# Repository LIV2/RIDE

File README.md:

# 🏍 RIDE - A500+ Fast Ram + IDE
## IDE + 11.37 Megabyte Fast RAM for the A500/A1000/A2000/CDTV

## Features
- 11.37MB Fast RAM - 1.5MB $C0/Ranger + 8MB Fast + 1.87 Bonus ($A00000)
- Autoboot IDE, Kick 1.3 compatible Open Source driver [lide.device](https://github.com/LIV2/lide.device)
- [Supports up to 2TB drives](https://github.com/LIV2/lide.device/#large-drive-4gb-support)
- Supports ATAPI Devices (CD/DVD-ROM, Zip disk etc - no IDEFix needed)
- Boot from ZIP/LS-120 etc
- [Boot from CD-ROM*](https://github.com/LIV2/lide.device/#boot-from-cdrom)
- SCSI Direct, NSD, TD64 support

## Table of contents
1. [Compatibility](#compatibility)
2. [Jumper settings](#jumper-settings)
3. [Connections](#connections)
4. [Enabling A0 Bonus RAM](#enabling-a0-bonus-ram)
5. [Programming](#programming)
6. [Ordering PCBs](#ordering-pcbs)
    * [PCB Order details](#pcb-order-details)
    * [PCB Assembly](#pcb-assembly)
    * [Bill of Materials](#bill-of-materials)
7. [License](#license)

## Compatibility

Compatible with Kickstart 1.3 and up.

## Jumper settings

**IDE Off**: Close to disable IDE  
**RAM1/RAM2**: Autoconfig RAM configuration
|RAM1|RAM2|Size|
|-|-|----|
|Open|Open|**8 MB**|
|Closed|Open|**4 MB**|
|Open|Closed|**2 MB**|
|Closed|Closed|**Disable**|

## Connections
* **LED**: Activity LED  
* **OVR**: **(Optional)** if connected this will enable the Ranger ($C00000) and Bonus ($A00000) RAM regions.  
Connect OVR to Gary pin 29 or pin 17 of the side expansion port  
* **CFGIN/OUT**: These pins allow this device to co-exist with other Autoconfig devices.
If there are no other Autoconfig devices in your system you can just leave these unconnected.  
If there *are* other Autoconfig devices you will want to use one of these to add the device to the chain.<br /><br />
In the Amiga 2000 you can connect CFGIN to U606 Pin 8 which will add the device to the end of the chain but **NOTE: This takes up the config signal for the leftmost slot (CN601) so do NOT install a Zorro card there**

## Enabling A0 Bonus RAM
The A0 Bonus RAM is not automatically picked up by kickstart and needs to be added using one of the included utilities.  
Note that the `addmem` command from Aminet will **NOT** work - the memory is not enabled until a specific RIDE register is set to enable it

To add the A0 Bonus RAM to the system you will need to use the `addram` command included in the RIDE-Software adf/lha found under [Releases](https://github.com/LIV2/RIDE/releases/latest).

Alternatively you can add the `bootrom` module to a custom kickstart so that this is done automatically at every boot.

## Programming

Program the CPLD using the relevant .jed file below (Right-click, Save as)
|Model|File|
|-----|----|
|A500(+)<br />A1000<br />A2000|[RIDE.jed](https://github.com/LIV2/RIDE/raw/master/Binary/RIDE.jed)|
|CDTV|[RIDE-CDTV.jed](https://github.com/LIV2/RIDE/raw/master/Binary/RIDE-CDTV.jed)|

You can find instructions on how to do that [here](https://linuxjedi.co.uk/2020/12/01/programming-xilinx-jtag-from-a-raspberry-pi/)

The IDE ROM can be programmed by booting from the latest lide-update.adf [here](https://github.com/LIV2/LIDE.device/releases/latest).

## Ordering PCBs

Download the latest Gerbers.zip from the latest release listed on the right-hand side of this page.

Also included in the release are the placement and bom files needed for JLCPCB's assembly service

### PCB Order details
This PCB has been designed to JLCPCB's 4-layer capabilities so I recommend ordering from them

* Layers: 4
* Surface finish: ENIG
* Remove Order Number: Yes

### PCB Assembly
The release files include the relevant BOM and CPL files for JLCPCB's Assembly service  
You can use the following options:  
* PCBA Type: Economic
* Assembly side: Top side
* Confirm Parts Placement: Yes (I recommend checking that all ICs have pin 1 in the correct location etc)

### Bill of materials
**Note**:
* The BOM lists a Mill-Max part for the pin sockets, however you can substitute these for some 9.7mm pin sockets like [these](https://www.aliexpress.com/item/33019740866.html?spm=a2g0o.productlist.similar_items.43.4ce068b4xz903H&utparam-url=scene%3Aimage_search%7Cquery_from%3Adetail_bigimg&pdp_npi=4%40dis%21NZD%2116.79%217.71%21%21%219.24%214.24%21%402101c67a17357902339972308e0382%2167156399241%21sea%21NZ%210%21ABX)  
* The 39SF010 flash can be substituted with 39SF020 or 39SF040 in TSOP-32

[BOM](https://html-preview.github.io/?url=https://github.com/LIV2/RIDE/blob/master/Docs/RIDE_bom.html)  
[HTML Interactive BOM](https://html-preview.github.io/?url=https://github.com/LIV2/RIDE/blob/master/Docs/RIDE-ibom.html)

## Acknowledgements
Thanks to [SukkoPera](https://github.com/SukkoPera) for supporting my early IDE prototype.

## License

This project is licensed under the GPL-2.0 only license

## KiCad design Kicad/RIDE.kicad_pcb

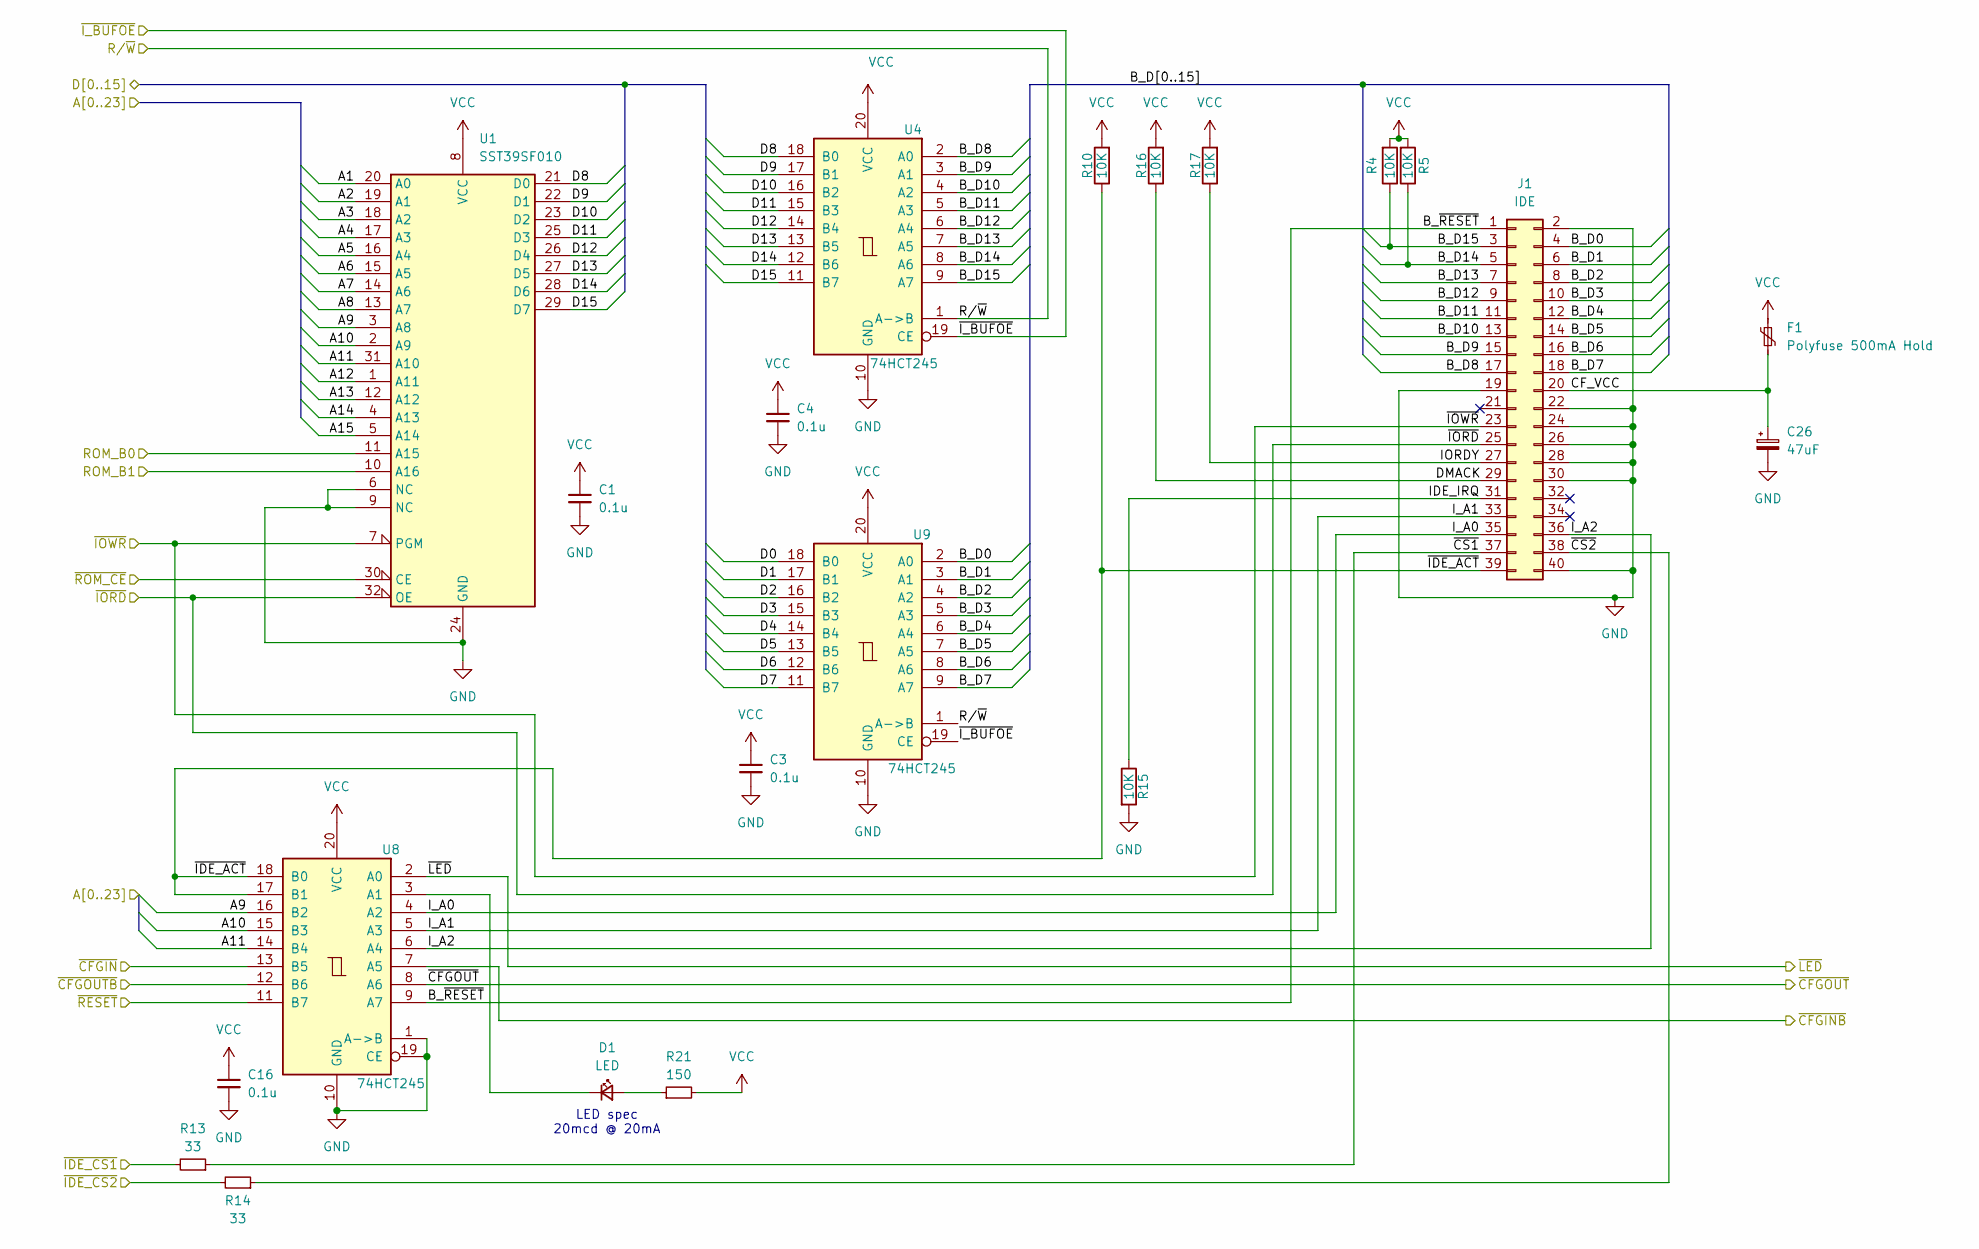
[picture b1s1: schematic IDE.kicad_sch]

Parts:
C1, C3, C4, C16: 0.1u; C_0603_1608Metric; Mouser # 80-C603C104K5RAC3121; LCSC # C14663
C26: 47uF; CP_EIA-3216-18_Kemet-A_Pad1.58x1.35mm_HandSolder; Mouser # 80-T490A476M10ATE1K; LCSC # C193224
D1: LED; LED_0603_1608Metric; Mouser # 696-SML-LX0603GW; LCSC # C136120
F1: Polyfuse 500mA Hold; Fuse_1206_3216Metric_Pad1.42x1.75mm_HandSolder; Mouser # 576-1206L110-16WR
J1: IDE; IDC-Header_2x20_P2.54mm_Vertical; Mouser # 737-BHR-40-VUA
R4, R5, R10, R15, R16, R17: 10K; R_0603_1608Metric; Mouser # 279-CRGH0603J10K; LCSC # C25804
R13, R14: 33; R_0603_1608Metric; Mouser # 279-CRG0603F33R; LCSC # C23140
R21: 150; R_0603_1608Metric; Mouser # 279-CRGP0603F150R; LCSC # C22808
U1: SST39SF010; TSOP-I-32_11.8x8mm_P0.5mm; Digikey # 150-SST39SF010A-70-4C-TU-ND
U4, U8, U9: 74HCT245; TSSOP-20_4.4x6.5mm_P0.65mm; Mouser # 595-SN74HCT245PWR; LCSC # C6779

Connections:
/CPLD/A1: U1.20 (A0); also elsewhere on the board
/CPLD/A2: U1.19 (A1); also elsewhere on the board
/CPLD/A3: U1.18 (A2); also elsewhere on the board
/CPLD/A4: U1.17 (A3); also elsewhere on the board
/CPLD/A5: U1.16 (A4); also elsewhere on the board
/CPLD/A6: U1.15 (A5); also elsewhere on the board
/CPLD/A7: U1.14 (A6); also elsewhere on the board
/CPLD/A8: U1.13 (A7); also elsewhere on the board
/CPLD/A9: U1.3 (A8), U8.16 (B2); also elsewhere on the board
/CPLD/A10: U1.2 (A9), U8.15 (B3); also elsewhere on the board
/CPLD/A11: U1.31 (A10), U8.14 (B4); also elsewhere on the board
/CPLD/A12: U1.1 (A11); also elsewhere on the board
/CPLD/A13: U1.12 (A12); also elsewhere on the board
/CPLD/A14: U1.4 (A13); also elsewhere on the board
/CPLD/A15: U1.5 (A14); also elsewhere on the board
/CPLD/D0: U9.18 (B0); also elsewhere on the board
/CPLD/D1: U9.17 (B1); also elsewhere on the board
/CPLD/D2: U9.16 (B2); also elsewhere on the board
/CPLD/D3: U9.15 (B3); also elsewhere on the board
/CPLD/D4: U9.14 (B4); also elsewhere on the board
/CPLD/D5: U9.13 (B5); also elsewhere on the board
/CPLD/D6: U9.12 (B6); also elsewhere on the board
/CPLD/D7: U9.11 (B7); also elsewhere on the board
/CPLD/D8: U1.21 (D0), U4.18 (B0); also elsewhere on the board
/CPLD/D9: U1.22 (D1), U4.17 (B1); also elsewhere on the board
/CPLD/D10: U1.23 (D2), U4.16 (B2); also elsewhere on the board
/CPLD/D11: U1.25 (D3), U4.15 (B3); also elsewhere on the board
/CPLD/D12: U1.26 (D4), U4.14 (B4); also elsewhere on the board
/CPLD/D13: U1.27 (D5), U4.13 (B5); also elsewhere on the board
/CPLD/D14: U1.28 (D6), U4.12 (B6); also elsewhere on the board
/CPLD/D15: U1.29 (D7), U4.11 (B7); also elsewhere on the board
/CPLD/ROM_B0: U1.11 (A15); also elsewhere on the board
/CPLD/ROM_B1: U1.10 (A16); also elsewhere on the board
/CPLD/R/~W: U4.1 (A->B), U9.1 (A->B); also elsewhere on the board
/CPLD/~CFGINB: U8.7 (A5); also elsewhere on the board
/CPLD/~CFGIN: U8.13 (B5); also elsewhere on the board
/CPLD/~CFGOUTB: U8.12 (B6); also elsewhere on the board
/CPLD/~IDE_CS1: R13.2; also elsewhere on the board
/CPLD/~IDE_CS2: R14.2; also elsewhere on the board
/CPLD/~I_BUFOE: U4.19 (CE), U9.19 (CE); also elsewhere on the board
/CPLD/~RESET: U8.11 (B7); also elsewhere on the board
/CPLD/~ROM_CE: U1.30 (CE); also elsewhere on the board
/IDE/B_D0: J1.4, U9.2 (A0)
/IDE/B_D1: J1.6, U9.3 (A1)
/IDE/B_D2: J1.8, U9.4 (A2)
/IDE/B_D3: J1.10, U9.5 (A3)
/IDE/B_D4: J1.12, U9.6 (A4)
/IDE/B_D5: J1.14, U9.7 (A5)
/IDE/B_D6: J1.16, U9.8 (A6)
/IDE/B_D7: J1.18, U9.9 (A7)
/IDE/B_D8: J1.17, U4.2 (A0)
/IDE/B_D9: J1.15, U4.3 (A1)
/IDE/B_D10: J1.13, U4.4 (A2)
/IDE/B_D11: J1.11, U4.5 (A3)
/IDE/B_D12: J1.9, U4.6 (A4)
/IDE/B_D13: J1.7, U4.7 (A5)
/IDE/B_D14: J1.5, R5.1, U4.8 (A6)
/IDE/B_D15: J1.3, R4.1, U4.9 (A7)
/IDE/B_~RESET: J1.1, U8.9 (A7)
/IDE/CF_VCC: C26.1, F1.2, J1.20
/IDE/DMACK: J1.29, R16.1
/IDE/IDE_IRQ: J1.31, R15.1
/IDE/IORDY: J1.27, R17.1
/IDE/I_A0: J1.35, U8.4 (A2)
/IDE/I_A1: J1.33, U8.5 (A3)
/IDE/I_A2: J1.36, U8.6 (A4)
/IDE/~CFGOUT: U8.8 (A6); also elsewhere on the board
/IDE/~CS1: J1.37, R13.1
/IDE/~CS2: J1.38, R14.1
/IDE/~IDE_ACT: J1.39, R10.1, U8.17 (B1), U8.18 (B0)
/IDE/~IORD: J1.25, U1.32 (OE); also elsewhere on the board
/IDE/~IOWR: J1.23, U1.7 (PGM); also elsewhere on the board
/IDE/~LED: U8.2 (A0); also elsewhere on the board
GND: C1.2, C3.2, C4.2, C16.2, C26.2, J1.2, J1.19, J1.22, J1.24, J1.26, J1.28, J1.30, J1.40, R15.2, U1.6 (NC), U1.9 (NC), U1.24 (GND), U4.10 (GND), U8.1 (A->B), U8.10 (GND), U8.19 (CE), U9.10 (GND); also elsewhere on the board
unnamed: D1.2 (A), R21.1
unnamed: D1.1 (K), U8.3 (A1)
VCC: C1.1, C3.1, C4.1, C16.1, F1.1, R4.2, R5.2, R10.2, R16.2, R17.2, R21.2, U1.8 (VCC), U4.20 (VCC), U8.20 (VCC), U9.20 (VCC); also elsewhere on the board

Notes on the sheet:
LED spec 20mcd @ 20mA

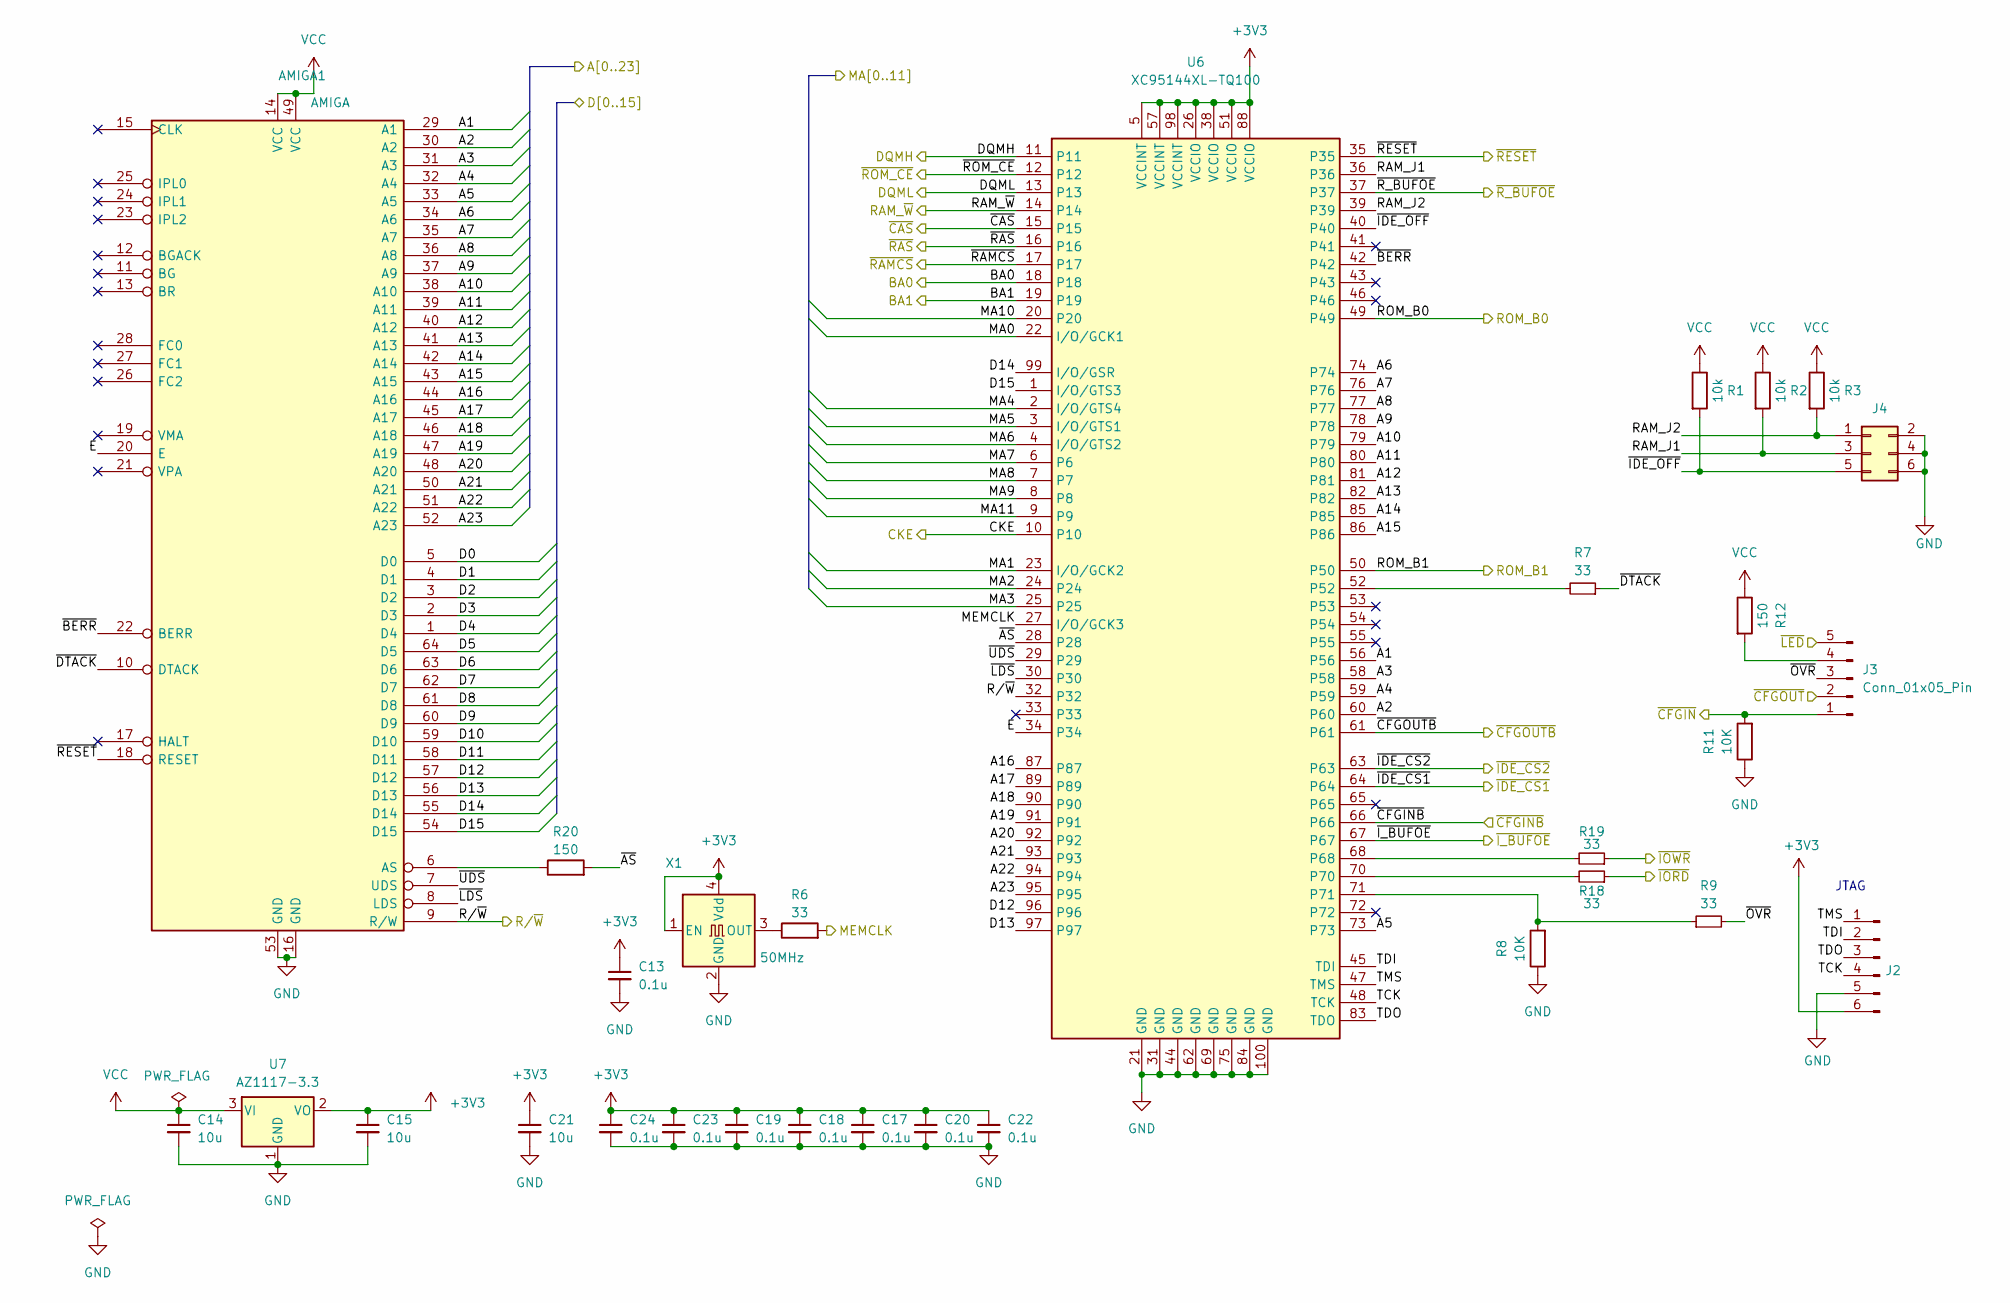
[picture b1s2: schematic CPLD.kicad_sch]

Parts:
AMIGA1: AMIGA; DIP-64_W22.86mm; Mouser # 575-643166
C13, C17, C18, C19, C20, C22, C23, C24: 0.1u; C_0603_1608Metric; Mouser # 80-C603C104K5RAC3121; LCSC # C14663
C14, C15: 10u; CP_EIA-3216-18_Kemet-A; Mouser # 80-T491A106M020; LCSC # C117023
C21: 10u; C_0805_2012Metric_Pad1.18x1.45mm_HandSolder; Mouser # 187-CL21A106KQFNNWE; LCSC # C15850
J2: Conn_01x06_Male; PinHeader_1x06_P2.54mm_Vertical
J3: Conn_01x05_Pin; PinHeader_1x05_P2.54mm_Vertical
J4: Conn_02x03_Odd_Even; PinHeader_2x03_P2.54mm_Vertical; Mouser # 571-4-146262-1
R1, R2, R3: 10k; R_0603_1608Metric; Mouser # 279-CRGH0603J10K; LCSC # C25804
R6, R7, R9, R18, R19: 33; R_0603_1608Metric; Mouser # 279-CRG0603F33R; LCSC # C23140
R8, R11: 10K; R_0603_1608Metric; Mouser # 279-CRGH0603J10K; LCSC # C25804
R12, R20: 150; R_0603_1608Metric; Mouser # 279-CRGP0603F150R; LCSC # C22808
U6: XC95144XL-TQ100; TQFP-100_14x14mm_P0.5mm; Mouser # 217-5144XL-10TQG100I; LCSC # C45126
U7: AZ1117-3.3; SOT-89-3; Mouser # 621-AZ1117CR-3.3TRG1; LCSC # C460428
X1: 50MHz; Oscillator_SMD_Abracon_ASE-4Pin_3.2x2.5mm; Mouser # 520-ECS-2333-500-BNT; LCSC # C5203552

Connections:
+3V3: C13.1, C15.1, C17.1, C18.1, C19.1, C20.1, C21.1, C22.1, C23.1, C24.1, J2.6, U6.5 (VCCINT), U6.26 (VCCIO), U6.38 (VCCIO), U6.51 (VCCIO), U6.57 (VCCINT), U6.88 (VCCIO), U6.98 (VCCINT), U7.2 (VO), X1.1 (EN), X1.4 (Vdd); also elsewhere on the board
/CPLD/A1: AMIGA1.29 (A1), U6.56; also elsewhere on the board
/CPLD/A2: AMIGA1.30 (A2), U6.60; also elsewhere on the board
/CPLD/A3: AMIGA1.31 (A3), U6.58; also elsewhere on the board
/CPLD/A4: AMIGA1.32 (A4), U6.59; also elsewhere on the board
/CPLD/A5: AMIGA1.33 (A5), U6.73; also elsewhere on the board
/CPLD/A6: AMIGA1.34 (A6), U6.74; also elsewhere on the board
/CPLD/A7: AMIGA1.35 (A7), U6.76; also elsewhere on the board
/CPLD/A8: AMIGA1.36 (A8), U6.77; also elsewhere on the board
/CPLD/A9: AMIGA1.37 (A9), U6.78; also elsewhere on the board
/CPLD/A10: AMIGA1.38 (A10), U6.79; also elsewhere on the board
/CPLD/A11: AMIGA1.39 (A11), U6.80; also elsewhere on the board
/CPLD/A12: AMIGA1.40 (A12), U6.81; also elsewhere on the board
/CPLD/A13: AMIGA1.41 (A13), U6.82; also elsewhere on the board
/CPLD/A14: AMIGA1.42 (A14), U6.85; also elsewhere on the board
/CPLD/A15: AMIGA1.43 (A15), U6.86; also elsewhere on the board
/CPLD/A16: AMIGA1.44 (A16), U6.87
/CPLD/A17: AMIGA1.45 (A17), U6.89
/CPLD/A18: AMIGA1.46 (A18), U6.90
/CPLD/A19: AMIGA1.47 (A19), U6.91
/CPLD/A20: AMIGA1.48 (A20), U6.92
/CPLD/A21: AMIGA1.50 (A21), U6.93
/CPLD/A22: AMIGA1.51 (A22), U6.94
/CPLD/A23: AMIGA1.52 (A23), U6.95
/CPLD/BA0: U6.18; also elsewhere on the board
/CPLD/BA1: U6.19; also elsewhere on the board
/CPLD/CKE: U6.10; also elsewhere on the board
/CPLD/D0: AMIGA1.5 (D0); also elsewhere on the board
/CPLD/D1: AMIGA1.4 (D1); also elsewhere on the board
/CPLD/D2: AMIGA1.3 (D2); also elsewhere on the board
/CPLD/D3: AMIGA1.2 (D3); also elsewhere on the board
/CPLD/D4: AMIGA1.1 (D4); also elsewhere on the board
/CPLD/D5: AMIGA1.64 (D5); also elsewhere on the board
/CPLD/D6: AMIGA1.63 (D6); also elsewhere on the board
/CPLD/D7: AMIGA1.62 (D7); also elsewhere on the board
/CPLD/D8: AMIGA1.61 (D8); also elsewhere on the board
/CPLD/D9: AMIGA1.60 (D9); also elsewhere on the board
/CPLD/D10: AMIGA1.59 (D10); also elsewhere on the board
/CPLD/D11: AMIGA1.58 (D11); also elsewhere on the board
/CPLD/D12: AMIGA1.57 (D12), U6.96; also elsewhere on the board
/CPLD/D13: AMIGA1.56 (D13), U6.97; also elsewhere on the board
/CPLD/D14: AMIGA1.55 (D14), U6.99 (I/O/GSR); also elsewhere on the board
/CPLD/D15: AMIGA1.54 (D15), U6.1 (I/O/GTS3); also elsewhere on the board
/CPLD/DQMH: U6.11; also elsewhere on the board
/CPLD/DQML: U6.13; also elsewhere on the board
/CPLD/E: AMIGA1.20 (E), U6.34
/CPLD/MA0: U6.22 (I/O/GCK1); also elsewhere on the board
/CPLD/MA1: U6.23 (I/O/GCK2); also elsewhere on the board
/CPLD/MA2: U6.24; also elsewhere on the board
/CPLD/MA3: U6.25; also elsewhere on the board
/CPLD/MA4: U6.2 (I/O/GTS4); also elsewhere on the board
/CPLD/MA5: U6.3 (I/O/GTS1); also elsewhere on the board
/CPLD/MA6: U6.4 (I/O/GTS2); also elsewhere on the board
/CPLD/MA7: U6.6; also elsewhere on the board
/CPLD/MA8: U6.7; also elsewhere on the board
/CPLD/MA9: U6.8; also elsewhere on the board
/CPLD/MA10: U6.20; also elsewhere on the board
/CPLD/MA11: U6.9; also elsewhere on the board
/CPLD/MEMCLK: R6.2, U6.27 (I/O/GCK3); also elsewhere on the board
/CPLD/RAM_J1: J4.3, R2.2, U6.36
/CPLD/RAM_J2: J4.1, R3.2, U6.39
/CPLD/RAM_~W: U6.14; also elsewhere on the board
/CPLD/ROM_B0: U6.49; also elsewhere on the board
/CPLD/ROM_B1: U6.50; also elsewhere on the board
/CPLD/R/~W: AMIGA1.9 (R/W), U6.32; also elsewhere on the board
/CPLD/TCK: J2.4, U6.48 (TCK)
/CPLD/TDI: J2.2, U6.45 (TDI)
/CPLD/TDO: J2.3, U6.83 (TDO)
/CPLD/TMS: J2.1, U6.47 (TMS)
/CPLD/~AS: R20.2, U6.28
/CPLD/~BERR: AMIGA1.22 (BERR), U6.42
/CPLD/~CAS: U6.15; also elsewhere on the board
/CPLD/~CFGINB: U6.66; also elsewhere on the board
/CPLD/~CFGIN: J3.1, R11.2; also elsewhere on the board
/CPLD/~CFGOUTB: U6.61; also elsewhere on the board
/CPLD/~DTACK: AMIGA1.10 (DTACK), R7.1
/CPLD/~IDE_CS1: U6.64; also elsewhere on the board
/CPLD/~IDE_CS2: U6.63; also elsewhere on the board
/CPLD/~IDE_OFF: J4.5, R1.2, U6.40
/CPLD/~I_BUFOE: U6.67; also elsewhere on the board
/CPLD/~LDS: AMIGA1.8 (LDS), U6.30
/CPLD/~OVR: J3.3, R9.2
/CPLD/~RAMCS: U6.17; also elsewhere on the board
/CPLD/~RAS: U6.16; also elsewhere on the board
/CPLD/~RESET: AMIGA1.18 (RESET), U6.35; also elsewhere on the board
/CPLD/~ROM_CE: U6.12; also elsewhere on the board
/CPLD/~R_BUFOE: U6.37; also elsewhere on the board
/CPLD/~UDS: AMIGA1.7 (UDS), U6.29
/IDE/~CFGOUT: J3.2; also elsewhere on the board
/IDE/~IORD: R18.1; also elsewhere on the board
/IDE/~IOWR: R19.1; also elsewhere on the board
/IDE/~LED: J3.5; also elsewhere on the board
GND: AMIGA1.16 (GND), AMIGA1.53 (GND), C13.2, C14.2, C15.2, C17.2, C18.2, C19.2, C20.2, C21.2, C22.2, C23.2, C24.2, J2.5, J4.2, J4.4, J4.6, R8.1, R11.1, U6.21 (GND), U6.31 (GND), U6.44 (GND), U6.62 (GND), U6.69 (GND), U6.75 (GND), U6.84 (GND), U6.100 (GND), U7.1 (GND), X1.2 (GND); also elsewhere on the board
unnamed: AMIGA1.6 (AS), R20.1
unnamed: J3.4, R12.2
unnamed: R7.2, U6.52
unnamed: R19.2, U6.68
unnamed: R18.2, U6.70
unnamed: R8.2, R9.1, U6.71
unnamed: R6.1, X1.3 (OUT)
VCC: AMIGA1.14 (VCC), AMIGA1.49 (VCC), C14.1, R1.1, R2.1, R3.1, R12.1, U7.3 (VI); also elsewhere on the board

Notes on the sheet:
JTAG

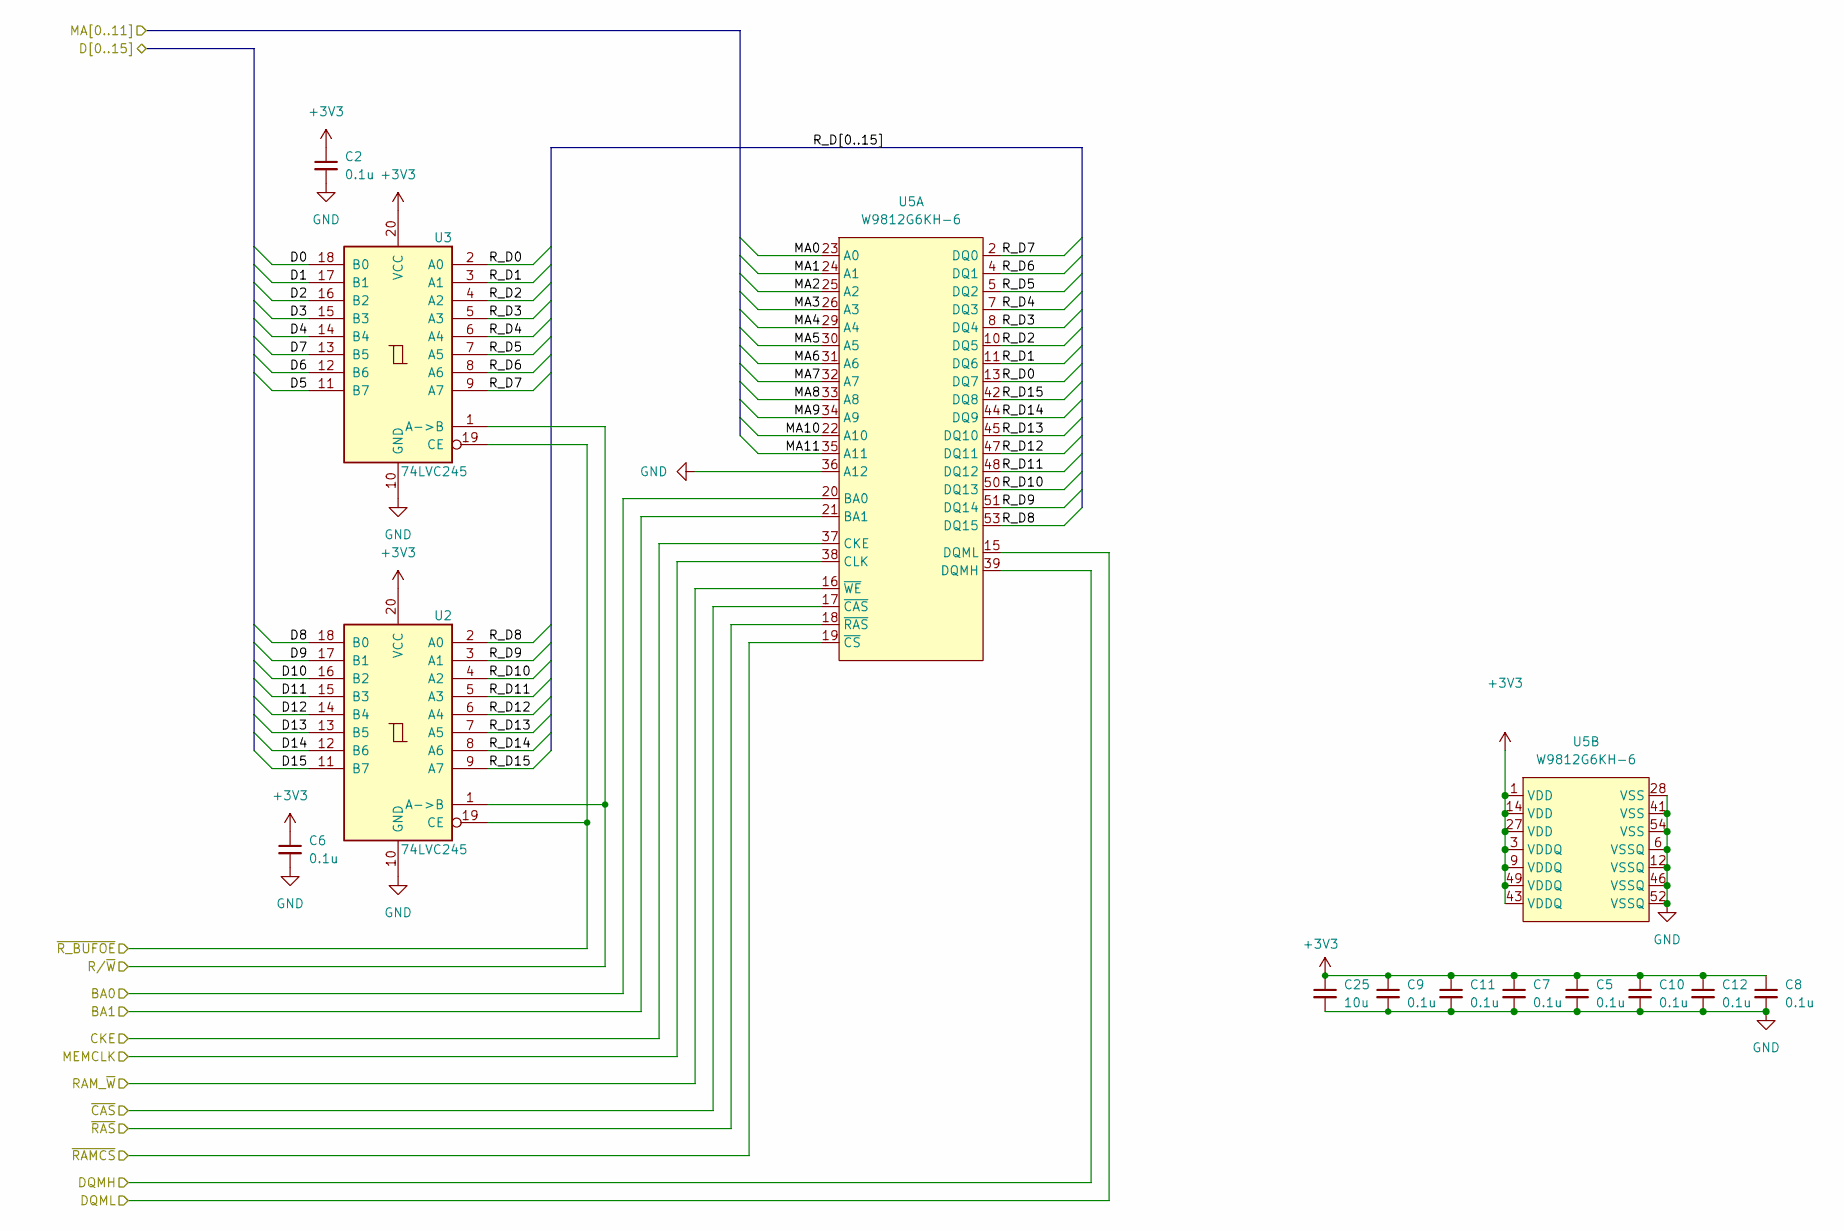
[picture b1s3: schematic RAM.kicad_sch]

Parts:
C2, C5, C6, C7, C8, C9, C10, C11, C12: 0.1u; C_0603_1608Metric; Mouser # 80-C603C104K5RAC3121; LCSC # C14663
C25: 10u; C_0805_2012Metric_Pad1.18x1.45mm_HandSolder; Mouser # 187-CL21A106KQFNNWE; LCSC # C15850
U2, U3: 74LVC245; TSSOP-20_4.4x6.5mm_P0.65mm; Mouser # 595-SN74LVC245APWR; LCSC # C7848
U5: W9812G6KH-6; TSOP-II-54_22.2x10.16mm_P0.8mm; Mouser # 454-W9812G6KH-6; LCSC # C62379

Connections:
+3V3: C2.1, C5.1, C6.1, C7.1, C8.1, C9.1, C10.1, C11.1, C12.1, C25.1, U2.20 (VCC), U3.20 (VCC), U5.1 (VDD), U5.3 (VDDQ), U5.9 (VDDQ), U5.14 (VDD), U5.27 (VDD), U5.43 (VDDQ), U5.49 (VDDQ); also elsewhere on the board
/CPLD/BA0: U5.20 (BA0); also elsewhere on the board
/CPLD/BA1: U5.21 (BA1); also elsewhere on the board
/CPLD/CKE: U5.37 (CKE); also elsewhere on the board
/CPLD/D0: U3.18 (B0); also elsewhere on the board
/CPLD/D1: U3.17 (B1); also elsewhere on the board
/CPLD/D2: U3.16 (B2); also elsewhere on the board
/CPLD/D3: U3.15 (B3); also elsewhere on the board
/CPLD/D4: U3.14 (B4); also elsewhere on the board
/CPLD/D5: U3.11 (B7); also elsewhere on the board
/CPLD/D6: U3.12 (B6); also elsewhere on the board
/CPLD/D7: U3.13 (B5); also elsewhere on the board
/CPLD/D8: U2.18 (B0); also elsewhere on the board
/CPLD/D9: U2.17 (B1); also elsewhere on the board
/CPLD/D10: U2.16 (B2); also elsewhere on the board
/CPLD/D11: U2.15 (B3); also elsewhere on the board
/CPLD/D12: U2.14 (B4); also elsewhere on the board
/CPLD/D13: U2.13 (B5); also elsewhere on the board
/CPLD/D14: U2.12 (B6); also elsewhere on the board
/CPLD/D15: U2.11 (B7); also elsewhere on the board
/CPLD/DQMH: U5.39 (DQMH); also elsewhere on the board
/CPLD/DQML: U5.15 (DQML); also elsewhere on the board
/CPLD/MA0: U5.23 (A0); also elsewhere on the board
/CPLD/MA1: U5.24 (A1); also elsewhere on the board
/CPLD/MA2: U5.25 (A2); also elsewhere on the board
/CPLD/MA3: U5.26 (A3); also elsewhere on the board
/CPLD/MA4: U5.29 (A4); also elsewhere on the board
/CPLD/MA5: U5.30 (A5); also elsewhere on the board
/CPLD/MA6: U5.31 (A6); also elsewhere on the board
/CPLD/MA7: U5.32 (A7); also elsewhere on the board
/CPLD/MA8: U5.33 (A8); also elsewhere on the board
/CPLD/MA9: U5.34 (A9); also elsewhere on the board
/CPLD/MA10: U5.22 (A10); also elsewhere on the board
/CPLD/MA11: U5.35 (A11); also elsewhere on the board
/CPLD/MEMCLK: U5.38 (CLK); also elsewhere on the board
/CPLD/RAM_~W: U5.16 (~WE); also elsewhere on the board
/CPLD/R/~W: U2.1 (A->B), U3.1 (A->B); also elsewhere on the board
/CPLD/~CAS: U5.17 (~CAS); also elsewhere on the board
/CPLD/~RAMCS: U5.19 (~CS); also elsewhere on the board
/CPLD/~RAS: U5.18 (~RAS); also elsewhere on the board
/CPLD/~R_BUFOE: U2.19 (CE), U3.19 (CE); also elsewhere on the board
/RAM/R_D0: U3.2 (A0), U5.13 (DQ7)
/RAM/R_D1: U3.3 (A1), U5.11 (DQ6)
/RAM/R_D2: U3.4 (A2), U5.10 (DQ5)
/RAM/R_D3: U3.5 (A3), U5.8 (DQ4)
/RAM/R_D4: U3.6 (A4), U5.7 (DQ3)
/RAM/R_D5: U3.7 (A5), U5.5 (DQ2)
/RAM/R_D6: U3.8 (A6), U5.4 (DQ1)
/RAM/R_D7: U3.9 (A7), U5.2 (DQ0)
/RAM/R_D8: U2.2 (A0), U5.53 (DQ15)
/RAM/R_D9: U2.3 (A1), U5.51 (DQ14)
/RAM/R_D10: U2.4 (A2), U5.50 (DQ13)
/RAM/R_D11: U2.5 (A3), U5.48 (DQ12)
/RAM/R_D12: U2.6 (A4), U5.47 (DQ11)
/RAM/R_D13: U2.7 (A5), U5.45 (DQ10)
/RAM/R_D14: U2.8 (A6), U5.44 (DQ9)
/RAM/R_D15: U2.9 (A7), U5.42 (DQ8)
GND: C2.2, C5.2, C6.2, C7.2, C8.2, C9.2, C10.2, C11.2, C12.2, C25.2, U2.10 (GND), U3.10 (GND), U5.6 (VSSQ), U5.12 (VSSQ), U5.28 (VSS), U5.36 (A12), U5.41 (VSS), U5.46 (VSSQ), U5.52 (VSSQ), U5.54 (VSS); also elsewhere on the board

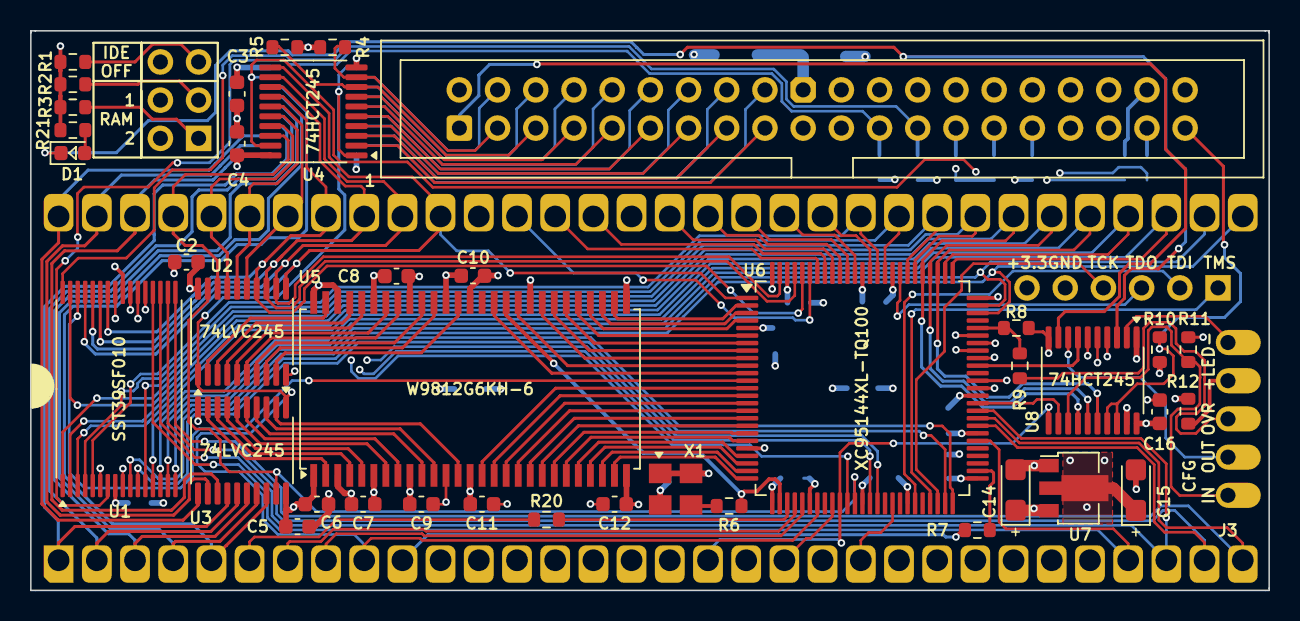
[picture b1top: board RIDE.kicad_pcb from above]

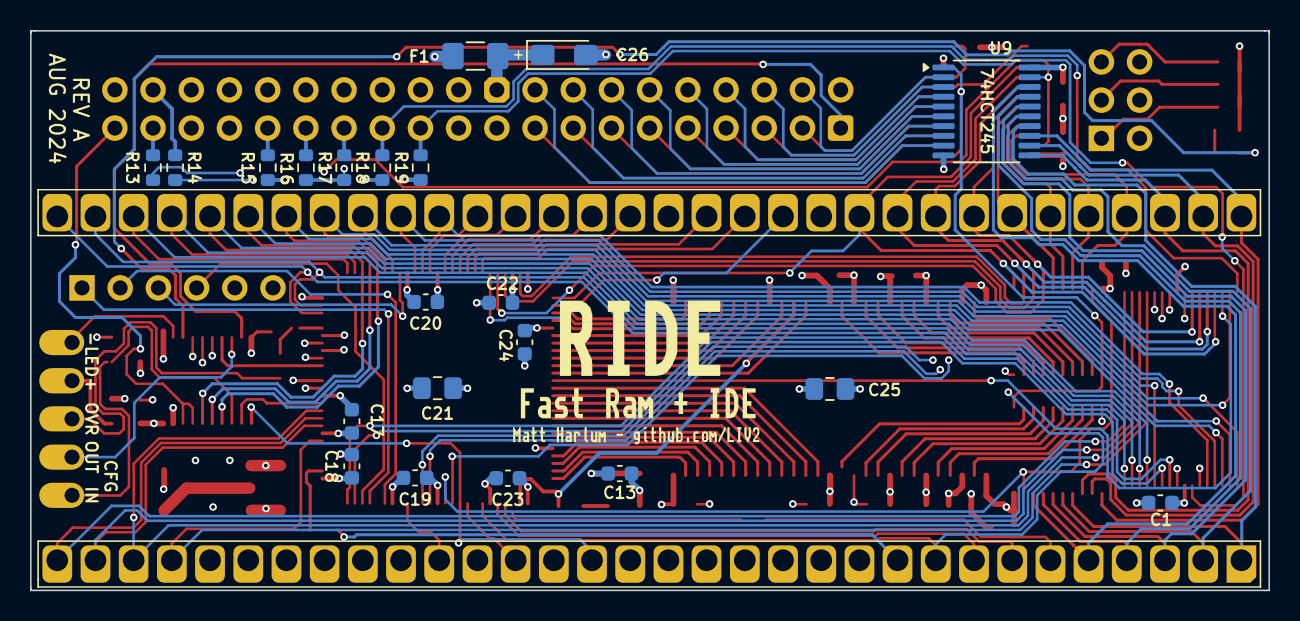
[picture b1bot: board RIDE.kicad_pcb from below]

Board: 4 copper layers, 82.3 x 37.2 mm, 67 parts (24 on the bottom side), 146 nets.

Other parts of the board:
kibuzzard-1: G***; kibuzzard-667ABBFF
kibuzzard-2: G***; kibuzzard-667CDE38
kibuzzard-3: G***; kibuzzard-667ABBF2

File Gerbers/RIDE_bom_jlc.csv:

"Qty","Comment","Designator","Footprint","LCSC Part #"
"21","0.1u","C1,C2,C3,C4,C5,C6,C7,C8,C9,C10,C11,C12,C13,C16,C17,C18,C19,C20,C22,C23,C24","C_0603_1608Metric","C14663"
"2","10u","C14,C15","CP_EIA-3216-18_Kemet-A","C117023"
"2","10u","C21,C25","C_0805_2012Metric_Pad1.18x1.45mm_HandSolder","C15850"
"1","47uF","C26","CP_EIA-3216-18_Kemet-A_Pad1.58x1.35mm_HandSolder","C193224"
"1","LED","D1","LED_0603_1608Metric","C136120"
"1","Polyfuse 500mA Hold","F1","Fuse_1206_3216Metric_Pad1.42x1.75mm_HandSolder","C21714343"
"1","Conn_02x03_Odd_Even","J4","PinHeader_2x03_P2.54mm_Vertical","C7501274"
"1","IDE","J1","IDC-Header_2x20_P2.54mm_Vertical","C9138"
"7","33","R6,R7,R9,R13,R14,R18,R19","R_0603_1608Metric","C23140"
"3","150","R12,R20,R21","R_0603_1608Metric","C22808"
"11","10k","R1,R2,R3,R4,R5,R8,R10,R11,R15,R16,R17","R_0603_1608Metric","C25804"
"3","74HCT245","U4,U8,U9","TSSOP-20_4.4x6.5mm_P0.65mm","C6779"
"2","74LVC245","U2,U3","TSSOP-20_4.4x6.5mm_P0.65mm","C7848"
"1","AZ1117-3.3","U7","SOT-89-3","C460428"
"1","SST39SF010","U1","TSOP-I-32_11.8x8mm_P0.5mm",""
"1","W9812G6KH-6","U5","TSOP-II-54_22.2x10.16mm_P0.8mm","C62379"
"1","XC95144XL-TQ100","U6","TQFP-100_14x14mm_P0.5mm","C45126"
"1","50MHz","X1","Oscillator_SMD_Abracon_ASE-4Pin_3.2x2.5mm","C5203552"

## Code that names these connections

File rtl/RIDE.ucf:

NET "DBUS<12>"    LOC = "P96";
NET "DBUS<13>"    LOC = "P97";
NET "DBUS<14>"    LOC = "P99";
NET "DBUS<15>"    LOC = "P1";
NET "ADDR<1>"     LOC = "P56";
NET "ADDR<2>"     LOC = "P60";
NET "ADDR<3>"     LOC = "P58";
NET "ADDR<4>"     LOC = "P59";
NET "ADDR<5>"     LOC = "P73";
NET "ADDR<6>"     LOC = "P74";
NET "ADDR<7>"     LOC = "P76";
NET "ADDR<8>"     LOC = "P77";
NET "ADDR<9>"     LOC = "P78";
NET "ADDR<10>"    LOC = "P79";
NET "ADDR<11>"    LOC = "P80";
NET "ADDR<12>"    LOC = "P81";
NET "ADDR<13>"    LOC = "P82";
NET "ADDR<14>"    LOC = "P85";
NET "ADDR<15>"    LOC = "P86";
NET "ADDR<16>"    LOC = "P87";
NET "ADDR<17>"    LOC = "P89";
NET "ADDR<18>"    LOC = "P90";
NET "ADDR<19>"    LOC = "P91";
NET "ADDR<20>"    LOC = "P92";
NET "ADDR<21>"    LOC = "P93";
NET "ADDR<22>"    LOC = "P94";
NET "ADDR<23>"    LOC = "P95";
NET "BERR_n"      LOC = "P42";
NET "UDS_n"       LOC = "P29";
NET "LDS_n"       LOC = "P30";
NET "RW"          LOC = "P32";
NET "AS_n"        LOC = "P28";
NET "RESET_n"     LOC = "P35";
NET "ECLK"        LOC = "P34";
NET "DTACK_n"     LOC = "P52";
NET "OVR_n"       LOC = "P71";
NET "CFGOUT_n"    LOC = "P61";
NET "CFGIN_n"     LOC = "P66";

NET "IDE_ENABLE"  LOC = "P40";
NET "IOR_n"       LOC = "P70";
NET "IOW_n"       LOC = "P68";
NET "IDECS1_n"    LOC = "P64";
NET "IDECS2_n"    LOC = "P63";
NET "IDEBUF_OE"   LOC = "P67";
NET "IDE_ROMEN"   LOC = "P12";
NET "ROM_BANK<0>" LOC = "P49";
NET "ROM_BANK<1>" LOC = "P50";
NET "MEMCLK"      LOC = "P27";

NET "RAM_SIZE<0>" LOC = "P36";
NET "RAM_SIZE<1>" LOC = "P39";

NET "MEMW_n"      LOC = "P14";
NET "RAS_n"       LOC = "P16";
NET "CAS_n"       LOC = "P15";
NET "CKE"         LOC = "P10";
NET "DQML"        LOC = "P13";
NET "DQMH"        LOC = "P11";
NET "RAMCS_n"     LOC = "P17";
NET "RAMOE_n"     LOC = "P37";
NET "BA<0>"       LOC = "P18";
NET "BA<1>"       LOC = "P19";
NET "MA<0>"       LOC = "P22";
NET "MA<1>"       LOC = "P23";
NET "MA<2>"       LOC = "P24";
NET "MA<3>"       LOC = "P25";
NET "MA<4>"       LOC = "P2";
NET "MA<5>"       LOC = "P3";
NET "MA<6>"       LOC = "P4";
NET "MA<7>"       LOC = "P6";
NET "MA<8>"       LOC = "P7";
NET "MA<9>"       LOC = "P8";
NET "MA<10>"      LOC = "P20";
NET "MA<11>"      LOC = "P9";

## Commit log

2024-12-31 Initial commit.
2024-12-31 Add Firmware build
2024-12-31 Update actions to build software
2025-01-02 Add CDTV Build
2025-01-02 Use assigned autoconfig product ids
2025-01-21 Update JLC BOM & CPL * Include IDE Header and jumper block * Replace JLC part numbers with in-stock items (except flash)
2025-12-04 Update BOM
    Add Digikey Part links (including new part number for Flash)
    Removed EOL flash part link from Mouser
2026-04-20 RTL: Register address decodes & optimize control register
    Greatly improves timing closure
